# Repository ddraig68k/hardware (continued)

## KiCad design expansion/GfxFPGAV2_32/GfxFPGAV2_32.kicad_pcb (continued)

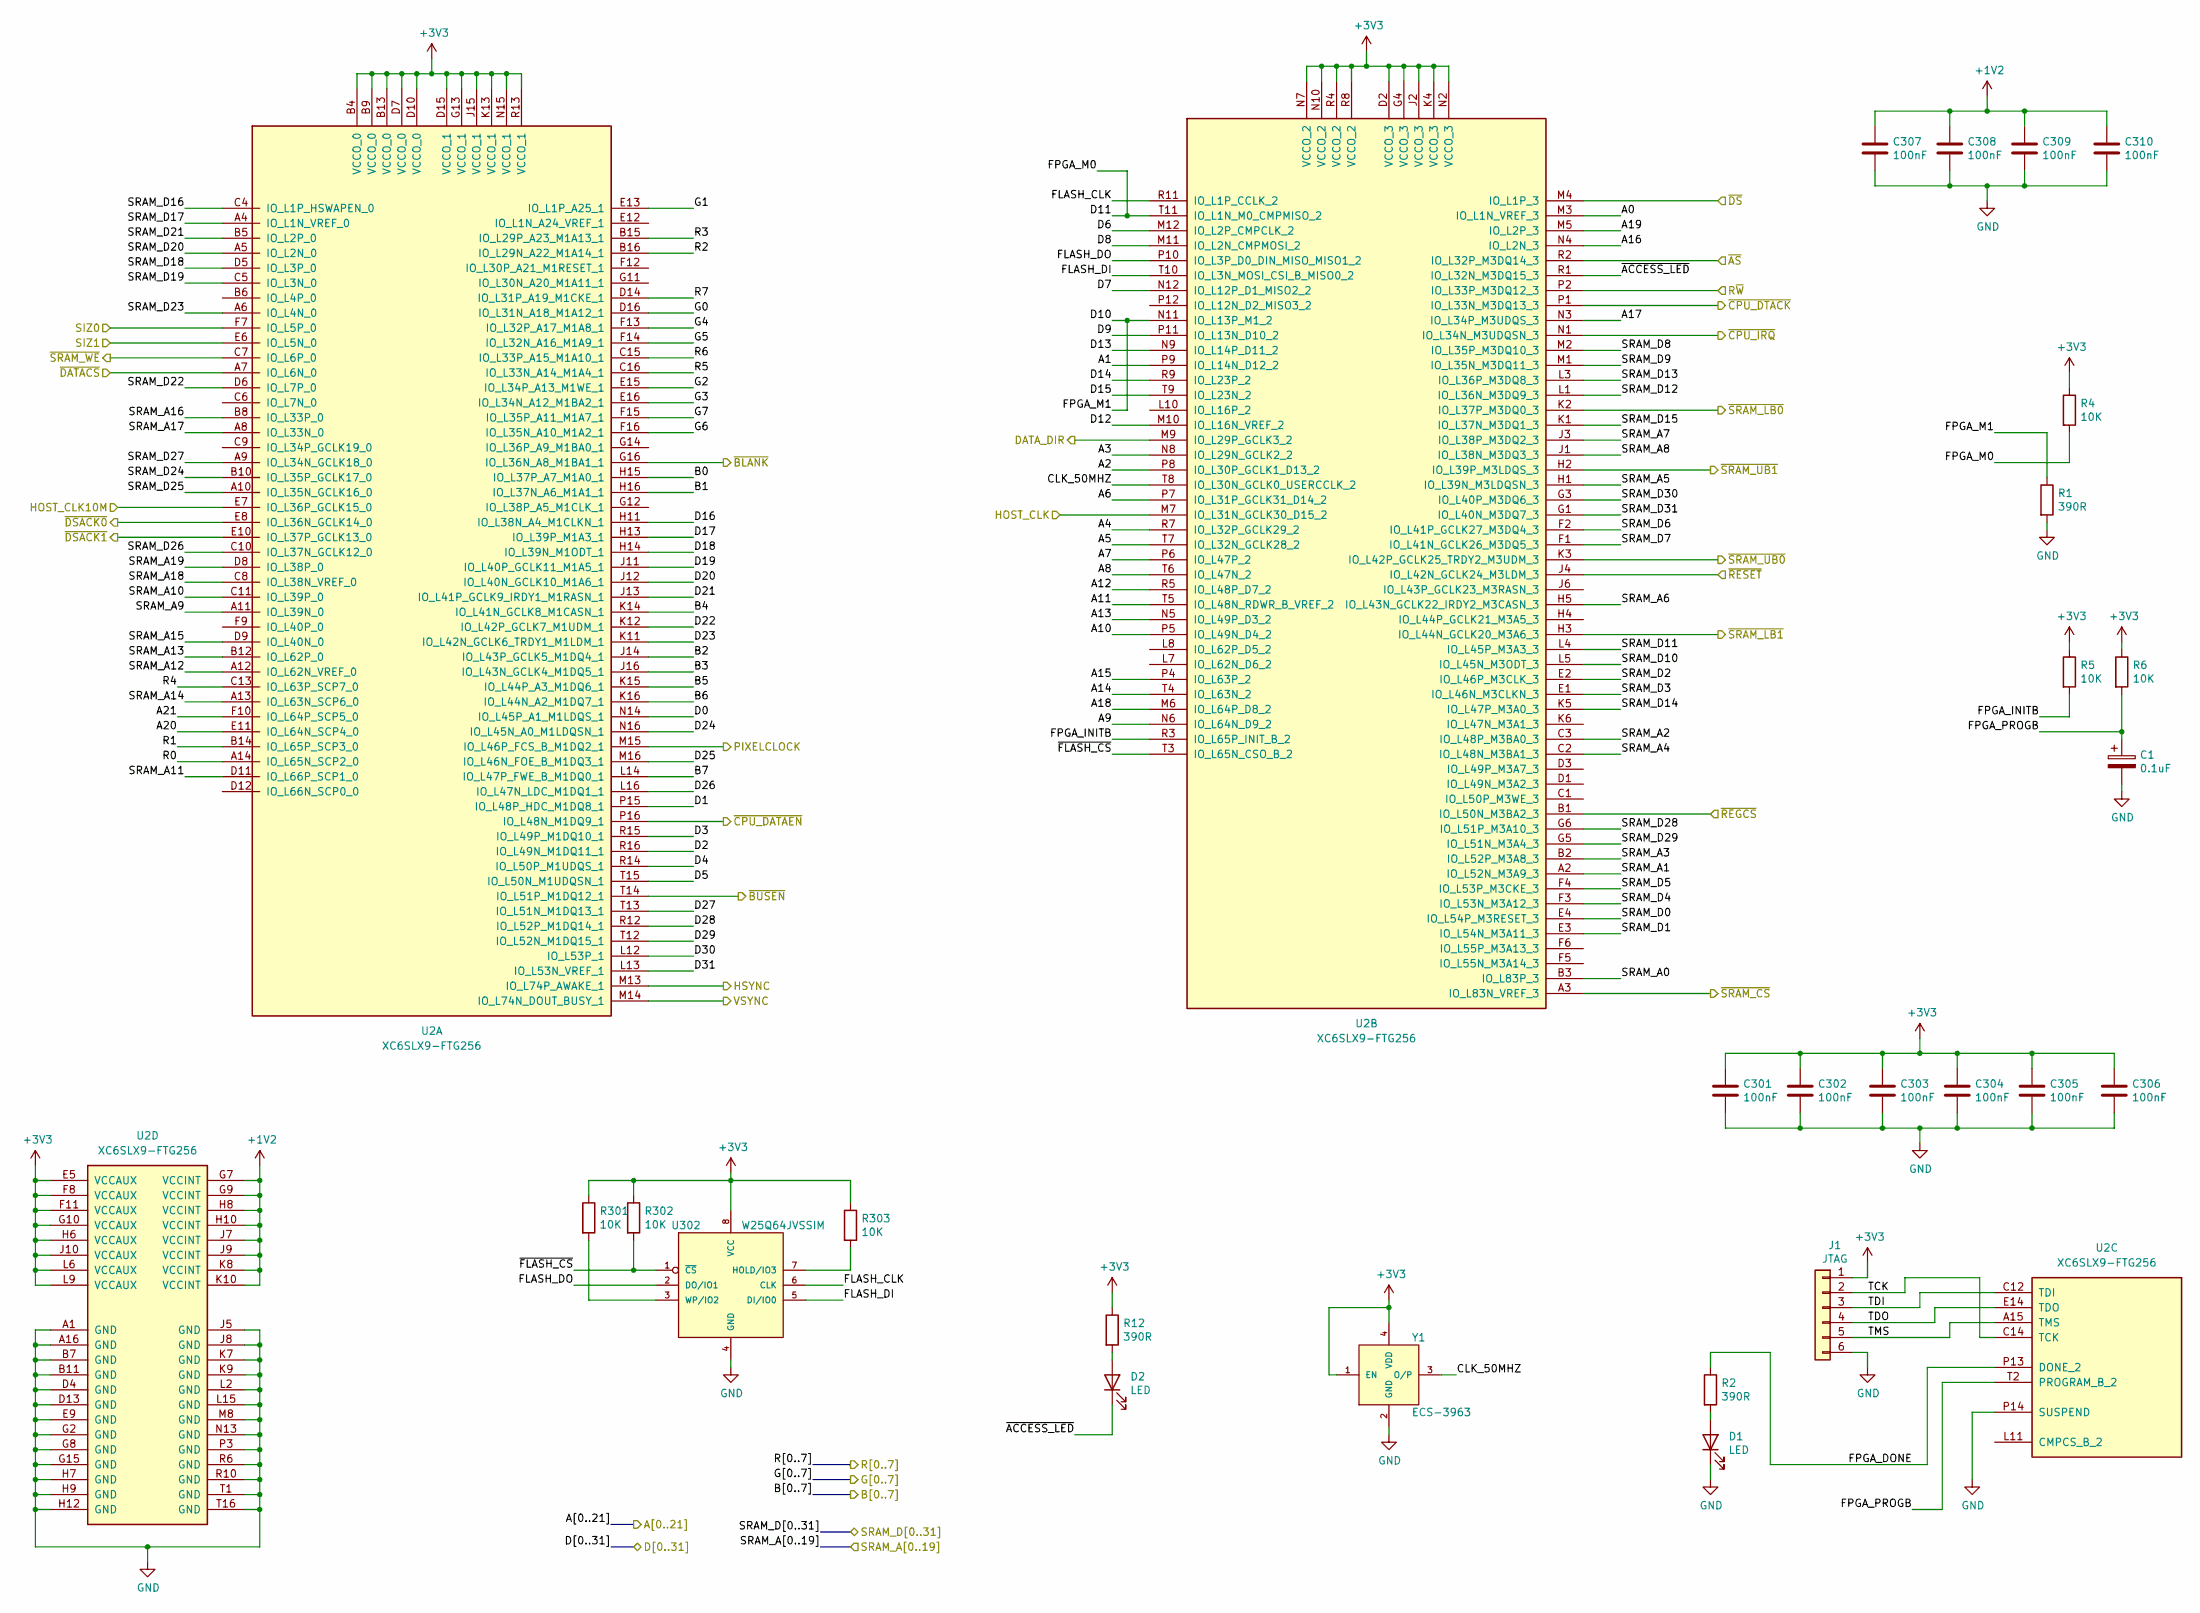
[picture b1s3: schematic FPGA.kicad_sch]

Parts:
C1: 0.1uF; CP_Elec_4x5.3
C301, C302, C303, C304, C305, C306, C307, C308, C309, C310: 100nF; C_0805_2012Metric
D1, D2: LED; LED_1206_3216Metric
J1: JTAG; PinHeader_1x06_P2.54mm_Vertical
R1, R2, R12: 390R; R_0805_2012Metric
R4, R5, R6, R301, R302, R303: 10K; R_0805_2012Metric
U2: XC6SLX9-FTG256; Xilinx_FTG256
U302: W25Q64JVSSIM; SOIC127P790X195-8N
Y1: ECS-3963; OSC_ECS-3963; PARTREV N/A

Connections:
+1V2: C307.1, C308.1, C309.1, C310.1, U2.G7 (VCCINT), U2.G9 (VCCINT), U2.H8 (VCCINT), U2.H10 (VCCINT), U2.J7 (VCCINT), U2.J9 (VCCINT), U2.K8 (VCCINT), U2.K10 (VCCINT); also elsewhere on the board
+3V3: C301.1, C302.1, C303.1, C304.1, C305.1, C306.1, J1.1, R4.1, R5.1, R6.1, R12.1, R301.1, R302.1, R303.1, U2.B4 (VCCO_0), U2.B9 (VCCO_0), U2.B13 (VCCO_0), U2.D2 (VCCO_3), U2.D7 (VCCO_0), U2.D10 (VCCO_0), U2.D15 (VCCO_1), U2.E5 (VCCAUX), U2.F8 (VCCAUX), U2.F11 (VCCAUX), U2.G4 (VCCO_3), U2.G10 (VCCAUX), U2.G13 (VCCO_1), U2.H6 (VCCAUX), U2.J2 (VCCO_3), U2.J10 (VCCAUX), U2.J15 (VCCO_1), U2.K4 (VCCO_3), U2.K13 (VCCO_1), U2.L6 (VCCAUX), U2.L9 (VCCAUX), U2.N2 (VCCO_3), U2.N7 (VCCO_2), U2.N10 (VCCO_2), U2.N15 (VCCO_1), U2.R4 (VCCO_2), U2.R8 (VCCO_2), U2.R13 (VCCO_1), U302.8 (VCC), Y1.1 (EN), Y1.4 (VDD); also elsewhere on the board
/FPGA/A0: U2.M3 (IO_L1N_VREF_3); also elsewhere on the board
/FPGA/A1: U2.P9 (IO_L14N_D12_2); also elsewhere on the board
/FPGA/A2: U2.P8 (IO_L30P_GCLK1_D13_2); also elsewhere on the board
/FPGA/A3: U2.N8 (IO_L29N_GCLK2_2); also elsewhere on the board
/FPGA/A4: U2.R7 (IO_L32P_GCLK29_2); also elsewhere on the board
/FPGA/A5: U2.T7 (IO_L32N_GCLK28_2); also elsewhere on the board
/FPGA/A6: U2.P7 (IO_L31P_GCLK31_D14_2); also elsewhere on the board
/FPGA/A7: U2.P6 (IO_L47P_2); also elsewhere on the board
/FPGA/A8: U2.T6 (IO_L47N_2); also elsewhere on the board
/FPGA/A9: U2.N6 (IO_L64N_D9_2); also elsewhere on the board
/FPGA/A10: U2.P5 (IO_L49N_D4_2); also elsewhere on the board
/FPGA/A11: U2.T5 (IO_L48N_RDWR_B_VREF_2); also elsewhere on the board
/FPGA/A12: U2.R5 (IO_L48P_D7_2); also elsewhere on the board
/FPGA/A13: U2.N5 (IO_L49P_D3_2); also elsewhere on the board
/FPGA/A14: U2.T4 (IO_L63N_2); also elsewhere on the board
/FPGA/A15: U2.P4 (IO_L63P_2); also elsewhere on the board
/FPGA/A16: U2.N4 (IO_L2N_3); also elsewhere on the board
/FPGA/A17: U2.N3 (IO_L34P_M3UDQS_3); also elsewhere on the board
/FPGA/A18: U2.M6 (IO_L64P_D8_2); also elsewhere on the board
/FPGA/A19: U2.M5 (IO_L2P_3); also elsewhere on the board
/FPGA/A20: U2.E11 (IO_L64N_SCP4_0); also elsewhere on the board
/FPGA/A21: U2.F10 (IO_L64P_SCP5_0); also elsewhere on the board
/FPGA/B0: U2.H15 (IO_L37P_A7_M1A0_1); also elsewhere on the board
/FPGA/B1: U2.H16 (IO_L37N_A6_M1A1_1); also elsewhere on the board
/FPGA/B2: U2.J14 (IO_L43P_GCLK5_M1DQ4_1); also elsewhere on the board
/FPGA/B3: U2.J16 (IO_L43N_GCLK4_M1DQ5_1); also elsewhere on the board
/FPGA/B4: U2.K14 (IO_L41N_GCLK8_M1CASN_1); also elsewhere on the board
/FPGA/B5: U2.K15 (IO_L44P_A3_M1DQ6_1); also elsewhere on the board
/FPGA/B6: U2.K16 (IO_L44N_A2_M1DQ7_1); also elsewhere on the board
/FPGA/B7: U2.L14 (IO_L47P_FWE_B_M1DQ0_1); also elsewhere on the board
/FPGA/CLK_50MHZ: U2.T8 (IO_L30N_GCLK0_USERCCLK_2), Y1.3 (O/P)
/FPGA/D0: U2.N14 (IO_L45P_A1_M1LDQS_1); also elsewhere on the board
/FPGA/D1: U2.P15 (IO_L48P_HDC_M1DQ8_1); also elsewhere on the board
/FPGA/D2: U2.R16 (IO_L49N_M1DQ11_1); also elsewhere on the board
/FPGA/D3: U2.R15 (IO_L49P_M1DQ10_1); also elsewhere on the board
/FPGA/D4: U2.R14 (IO_L50P_M1UDQS_1); also elsewhere on the board
/FPGA/D5: U2.T15 (IO_L50N_M1UDQSN_1); also elsewhere on the board
/FPGA/D6: U2.M12 (IO_L2P_CMPCLK_2); also elsewhere on the board
/FPGA/D7: U2.N12 (IO_L12P_D1_MISO2_2); also elsewhere on the board
/FPGA/D8: U2.M11 (IO_L2N_CMPMOSI_2); also elsewhere on the board
/FPGA/D9: U2.P11 (IO_L13N_D10_2); also elsewhere on the board
/FPGA/D10: R1.1, U2.N11 (IO_L13P_M1_2); also elsewhere on the board
/FPGA/D11: R4.2, U2.T11 (IO_L1N_M0_CMPMISO_2); also elsewhere on the board
/FPGA/D12: U2.M10 (IO_L16N_VREF_2); also elsewhere on the board
/FPGA/D13: U2.N9 (IO_L14P_D11_2); also elsewhere on the board
/FPGA/D14: U2.R9 (IO_L23P_2); also elsewhere on the board
/FPGA/D15: U2.T9 (IO_L23N_2); also elsewhere on the board
/FPGA/D16: U2.H11 (IO_L38N_A4_M1CLKN_1); also elsewhere on the board
/FPGA/D17: U2.H13 (IO_L39P_M1A3_1); also elsewhere on the board
/FPGA/D18: U2.H14 (IO_L39N_M1ODT_1); also elsewhere on the board
/FPGA/D19: U2.J11 (IO_L40P_GCLK11_M1A5_1); also elsewhere on the board
/FPGA/D20: U2.J12 (IO_L40N_GCLK10_M1A6_1); also elsewhere on the board
/FPGA/D21: U2.J13 (IO_L41P_GCLK9_IRDY1_M1RASN_1); also elsewhere on the board
/FPGA/D22: U2.K12 (IO_L42P_GCLK7_M1UDM_1); also elsewhere on the board
/FPGA/D23: U2.K11 (IO_L42N_GCLK6_TRDY1_M1LDM_1); also elsewhere on the board
/FPGA/D24: U2.N16 (IO_L45N_A0_M1LDQSN_1); also elsewhere on the board
/FPGA/D25: U2.M16 (IO_L46N_FOE_B_M1DQ3_1); also elsewhere on the board
/FPGA/D26: U2.L16 (IO_L47N_LDC_M1DQ1_1); also elsewhere on the board
/FPGA/D27: U2.T13 (IO_L51N_M1DQ13_1); also elsewhere on the board
/FPGA/D28: U2.R12 (IO_L52P_M1DQ14_1); also elsewhere on the board
/FPGA/D29: U2.T12 (IO_L52N_M1DQ15_1); also elsewhere on the board
/FPGA/D30: U2.L12 (IO_L53P_1); also elsewhere on the board
/FPGA/D31: U2.L13 (IO_L53N_VREF_1); also elsewhere on the board
/FPGA/DATA_DIR: U2.M9 (IO_L29P_GCLK3_2); also elsewhere on the board
/FPGA/FLASH_CLK: U2.R11 (IO_L1P_CCLK_2), U302.6 (CLK)
/FPGA/FLASH_DI: U2.T10 (IO_L3N_MOSI_CSI_B_MISO0_2), U302.5 (DI/IO0)
/FPGA/FLASH_DO: U2.P10 (IO_L3P_D0_DIN_MISO_MISO1_2), U302.2 (DO/IO1)
/FPGA/FPGA_DONE: R2.1, U2.P13 (DONE_2)
/FPGA/FPGA_INITB: R5.2, U2.R3 (IO_L65P_INIT_B_2)
/FPGA/FPGA_PROGB: C1.1, R6.2, U2.T2 (PROGRAM_B_2)
/FPGA/G0: U2.D16 (IO_L31N_A18_M1A12_1); also elsewhere on the board
/FPGA/G1: U2.E13 (IO_L1P_A25_1); also elsewhere on the board
/FPGA/G2: U2.E15 (IO_L34P_A13_M1WE_1); also elsewhere on the board
/FPGA/G3: U2.E16 (IO_L34N_A12_M1BA2_1); also elsewhere on the board
/FPGA/G4: U2.F13 (IO_L32P_A17_M1A8_1); also elsewhere on the board
/FPGA/G5: U2.F14 (IO_L32N_A16_M1A9_1); also elsewhere on the board
/FPGA/G6: U2.F16 (IO_L35N_A10_M1A2_1); also elsewhere on the board
/FPGA/G7: U2.F15 (IO_L35P_A11_M1A7_1); also elsewhere on the board
/FPGA/HOST_CLK: U2.M7 (IO_L31N_GCLK30_D15_2); also elsewhere on the board
/FPGA/HOST_CLK10M: U2.E7 (IO_L36P_GCLK15_0); also elsewhere on the board
/FPGA/HSYNC: U2.M13 (IO_L74P_AWAKE_1); also elsewhere on the board
/FPGA/PIXELCLOCK: U2.M15 (IO_L46P_FCS_B_M1DQ2_1); also elsewhere on the board
/FPGA/R0: U2.A14 (IO_L65N_SCP2_0); also elsewhere on the board
/FPGA/R1: U2.B14 (IO_L65P_SCP3_0); also elsewhere on the board
/FPGA/R2: U2.B16 (IO_L29N_A22_M1A14_1); also elsewhere on the board
/FPGA/R3: U2.B15 (IO_L29P_A23_M1A13_1); also elsewhere on the board
/FPGA/R4: U2.C13 (IO_L63P_SCP7_0); also elsewhere on the board
/FPGA/R5: U2.C16 (IO_L33N_A14_M1A4_1); also elsewhere on the board
/FPGA/R6: U2.C15 (IO_L33P_A15_M1A10_1); also elsewhere on the board
/FPGA/R7: U2.D14 (IO_L31P_A19_M1CKE_1); also elsewhere on the board
/FPGA/R~W: U2.P2 (IO_L33P_M3DQ12_3); also elsewhere on the board
/FPGA/SIZ0: U2.F7 (IO_L5P_0); also elsewhere on the board
/FPGA/SIZ1: U2.E6 (IO_L5N_0); also elsewhere on the board
/FPGA/SRAM_A0: U2.B3 (IO_L83P_3); also elsewhere on the board
/FPGA/SRAM_A1: U2.A2 (IO_L52N_M3A9_3); also elsewhere on the board
/FPGA/SRAM_A2: U2.C3 (IO_L48P_M3BA0_3); also elsewhere on the board
/FPGA/SRAM_A3: U2.B2 (IO_L52P_M3A8_3); also elsewhere on the board
/FPGA/SRAM_A4: U2.C2 (IO_L48N_M3BA1_3); also elsewhere on the board
/FPGA/SRAM_A5: U2.H1 (IO_L39N_M3LDQSN_3); also elsewhere on the board
/FPGA/SRAM_A6: U2.H5 (IO_L43N_GCLK22_IRDY2_M3CASN_3); also elsewhere on the board
/FPGA/SRAM_A7: U2.J3 (IO_L38P_M3DQ2_3); also elsewhere on the board
/FPGA/SRAM_A8: U2.J1 (IO_L38N_M3DQ3_3); also elsewhere on the board
/FPGA/SRAM_A9: U2.A11 (IO_L39N_0); also elsewhere on the board
/FPGA/SRAM_A10: U2.C11 (IO_L39P_0); also elsewhere on the board
/FPGA/SRAM_A11: U2.D11 (IO_L66P_SCP1_0); also elsewhere on the board
/FPGA/SRAM_A12: U2.A12 (IO_L62N_VREF_0); also elsewhere on the board
/FPGA/SRAM_A13: U2.B12 (IO_L62P_0); also elsewhere on the board
/FPGA/SRAM_A14: U2.A13 (IO_L63N_SCP6_0); also elsewhere on the board
/FPGA/SRAM_A15: U2.D9 (IO_L40N_0); also elsewhere on the board
/FPGA/SRAM_A16: U2.B8 (IO_L33P_0); also elsewhere on the board
/FPGA/SRAM_A17: U2.A8 (IO_L33N_0); also elsewhere on the board
/FPGA/SRAM_A18: U2.C8 (IO_L38N_VREF_0); also elsewhere on the board
/FPGA/SRAM_A19: U2.D8 (IO_L38P_0); also elsewhere on the board
/FPGA/SRAM_D0: U2.E4 (IO_L54P_M3RESET_3); also elsewhere on the board
/FPGA/SRAM_D1: U2.E3 (IO_L54N_M3A11_3); also elsewhere on the board
/FPGA/SRAM_D2: U2.E2 (IO_L46P_M3CLK_3); also elsewhere on the board
/FPGA/SRAM_D3: U2.E1 (IO_L46N_M3CLKN_3); also elsewhere on the board
/FPGA/SRAM_D4: U2.F3 (IO_L53N_M3A12_3); also elsewhere on the board
/FPGA/SRAM_D5: U2.F4 (IO_L53P_M3CKE_3); also elsewhere on the board
/FPGA/SRAM_D6: U2.F2 (IO_L41P_GCLK27_M3DQ4_3); also elsewhere on the board
/FPGA/SRAM_D7: U2.F1 (IO_L41N_GCLK26_M3DQ5_3); also elsewhere on the board
/FPGA/SRAM_D8: U2.M2 (IO_L35P_M3DQ10_3); also elsewhere on the board
/FPGA/SRAM_D9: U2.M1 (IO_L35N_M3DQ11_3); also elsewhere on the board
/FPGA/SRAM_D10: U2.L5 (IO_L45N_M3ODT_3); also elsewhere on the board
/FPGA/SRAM_D11: U2.L4 (IO_L45P_M3A3_3); also elsewhere on the board
/FPGA/SRAM_D12: U2.L1 (IO_L36N_M3DQ9_3); also elsewhere on the board
/FPGA/SRAM_D13: U2.L3 (IO_L36P_M3DQ8_3); also elsewhere on the board
/FPGA/SRAM_D14: U2.K5 (IO_L47P_M3A0_3); also elsewhere on the board
/FPGA/SRAM_D15: U2.K1 (IO_L37N_M3DQ1_3); also elsewhere on the board
/FPGA/SRAM_D16: U2.C4 (IO_L1P_HSWAPEN_0); also elsewhere on the board
/FPGA/SRAM_D17: U2.A4 (IO_L1N_VREF_0); also elsewhere on the board
/FPGA/SRAM_D18: U2.D5 (IO_L3P_0); also elsewhere on the board
/FPGA/SRAM_D19: U2.C5 (IO_L3N_0); also elsewhere on the board
/FPGA/SRAM_D20: U2.A5 (IO_L2N_0); also elsewhere on the board
/FPGA/SRAM_D21: U2.B5 (IO_L2P_0); also elsewhere on the board
/FPGA/SRAM_D22: U2.D6 (IO_L7P_0); also elsewhere on the board
/FPGA/SRAM_D23: U2.A6 (IO_L4N_0); also elsewhere on the board
/FPGA/SRAM_D24: U2.B10 (IO_L35P_GCLK17_0); also elsewhere on the board
/FPGA/SRAM_D25: U2.A10 (IO_L35N_GCLK16_0); also elsewhere on the board
/FPGA/SRAM_D26: U2.C10 (IO_L37N_GCLK12_0); also elsewhere on the board
/FPGA/SRAM_D27: U2.A9 (IO_L34N_GCLK18_0); also elsewhere on the board
/FPGA/SRAM_D28: U2.G6 (IO_L51P_M3A10_3); also elsewhere on the board
/FPGA/SRAM_D29: U2.G5 (IO_L51N_M3A4_3); also elsewhere on the board
/FPGA/SRAM_D30: U2.G3 (IO_L40P_M3DQ6_3); also elsewhere on the board
/FPGA/SRAM_D31: U2.G1 (IO_L40N_M3DQ7_3); also elsewhere on the board
/FPGA/TCK: J1.2, U2.C14 (TCK)
/FPGA/TDI: J1.3, U2.C12 (TDI)
/FPGA/TDO: J1.4, U2.E14 (TDO)
/FPGA/TMS: J1.5, U2.A15 (TMS)
/FPGA/VSYNC: U2.M14 (IO_L74N_DOUT_BUSY_1); also elsewhere on the board
/FPGA/~ACCESS_LED: D2.1 (K), U2.R1 (IO_L32N_M3DQ15_3)
/FPGA/~AS: U2.R2 (IO_L32P_M3DQ14_3); also elsewhere on the board
/FPGA/~BLANK: U2.G16 (IO_L36N_A8_M1BA1_1); also elsewhere on the board
/FPGA/~BUSEN: U2.T14 (IO_L51P_M1DQ12_1); also elsewhere on the board
/FPGA/~CPU_DATAEN: U2.P16 (IO_L48N_M1DQ9_1); also elsewhere on the board
/FPGA/~DATACS: U2.A7 (IO_L6N_0); also elsewhere on the board
/FPGA/~DS: U2.M4 (IO_L1P_3); also elsewhere on the board
/FPGA/~FLASH_CS: R302.2, U2.T3 (IO_L65N_CSO_B_2), U302.1 (~CS)
/FPGA/~REGCS: U2.B1 (IO_L50N_M3BA2_3); also elsewhere on the board
/FPGA/~RESET: U2.J4 (IO_L42N_GCLK24_M3LDM_3); also elsewhere on the board
/FPGA/~SRAM_CS: U2.A3 (IO_L83N_VREF_3); also elsewhere on the board
/FPGA/~SRAM_LB0: U2.K2 (IO_L37P_M3DQ0_3); also elsewhere on the board
/FPGA/~SRAM_LB1: U2.H3 (IO_L44N_GCLK20_M3A6_3); also elsewhere on the board
/FPGA/~SRAM_UB0: U2.K3 (IO_L42P_GCLK25_TRDY2_M3UDM_3); also elsewhere on the board
/FPGA/~SRAM_UB1: U2.H2 (IO_L39P_M3LDQS_3); also elsewhere on the board
/FPGA/~SRAM_WE: U2.C7 (IO_L6P_0); also elsewhere on the board
/~CPU_DSACK0: U2.E8 (IO_L36N_GCLK14_0); also elsewhere on the board
/~CPU_DSACK1: U2.E10 (IO_L37P_GCLK13_0); also elsewhere on the board
/~CPU_DTACK: U2.P1 (IO_L33N_M3DQ13_3); also elsewhere on the board
/~CPU_IRQ: U2.N1 (IO_L34N_M3UDQSN_3); also elsewhere on the board
GND: C1.2, C301.2, C302.2, C303.2, C304.2, C305.2, C306.2, C307.2, C308.2, C309.2, C310.2, D1.1 (K), J1.6, R1.2, U2.A1 (GND), U2.A16 (GND), U2.B7 (GND), U2.B11 (GND), U2.D4 (GND), U2.D13 (GND), U2.E9 (GND), U2.G2 (GND), U2.G8 (GND), U2.G15 (GND), U2.H7 (GND), U2.H9 (GND), U2.H12 (GND), U2.J5 (GND), U2.J8 (GND), U2.K7 (GND), U2.K9 (GND), U2.L2 (GND), U2.L15 (GND), U2.M8 (GND), U2.N13 (GND), U2.P3 (GND), U2.P14 (SUSPEND), U2.R6 (GND), U2.R10 (GND), U2.T1 (GND), U2.T16 (GND), U302.4 (GND), Y1.2 (GND); also elsewhere on the board
unnamed: D1.2 (A), R2.2
unnamed: D2.2 (A), R12.2
unnamed: R303.2, U302.7 (HOLD/IO3)
unnamed: R301.2, U302.3 (WP/IO2)

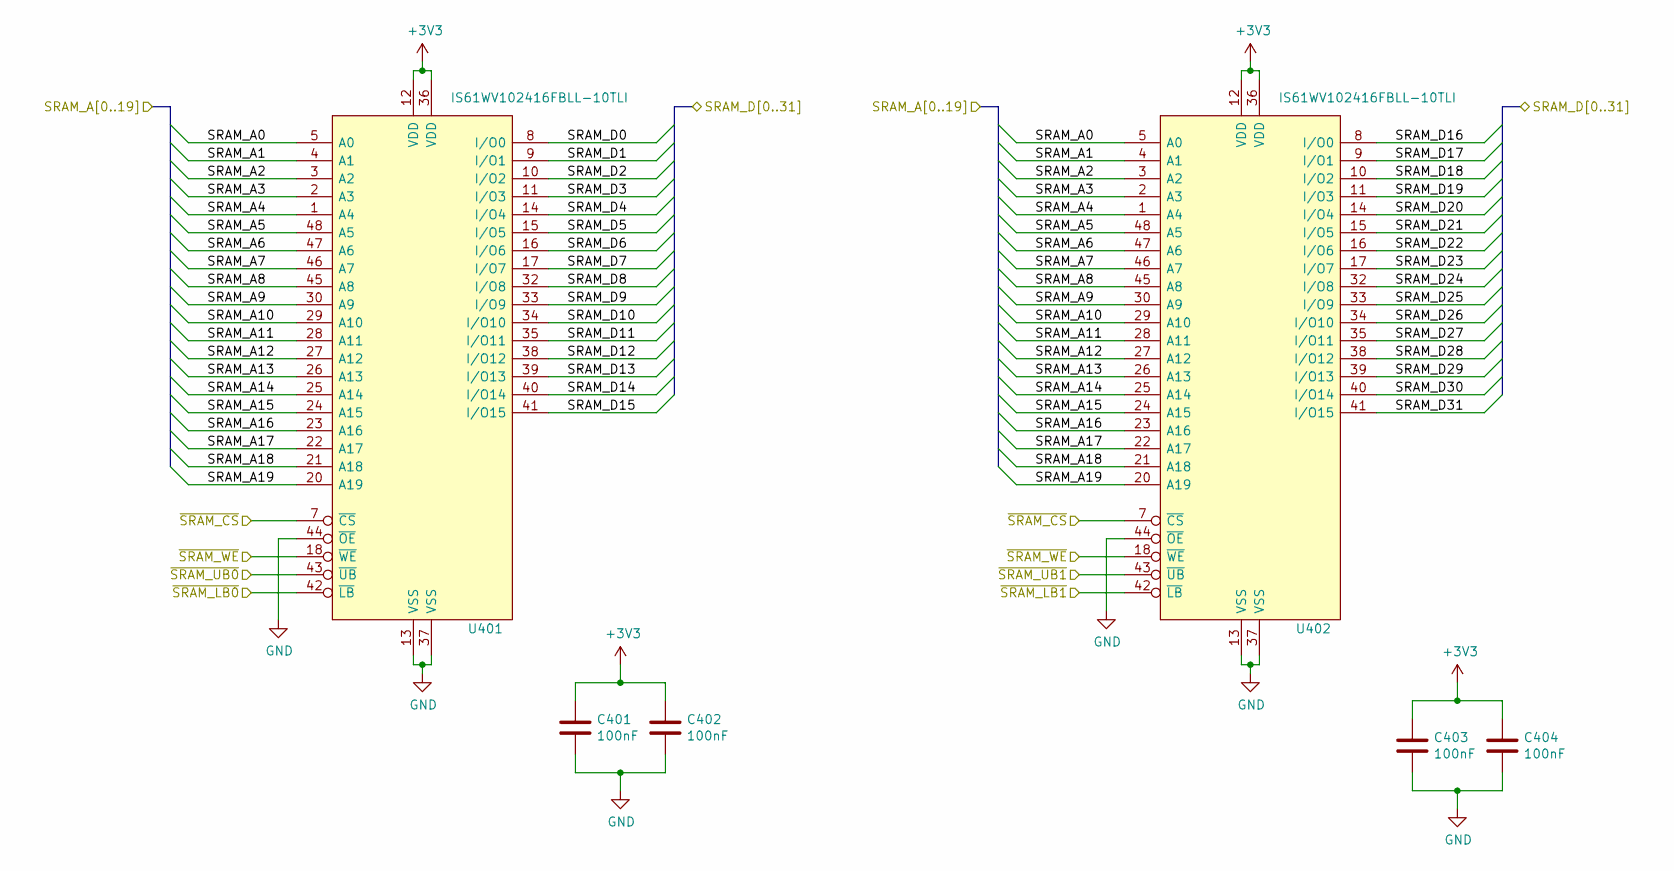
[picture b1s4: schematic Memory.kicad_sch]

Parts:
C401, C402, C403, C404: 100nF; C_0805_2012Metric
U401, U402: IS61WV102416FBLL-10TLI; SOP50P2000X120-48N; Manufacturer_Part_Number IS61WV102416FBLL-10TLI; Mouser Part Number 870-61WV12416FBL1TLI

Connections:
+3V3: C401.1, C402.1, C403.1, C404.1, U401.12 (VDD), U401.36 (VDD), U402.12 (VDD), U402.36 (VDD); also elsewhere on the board
/FPGA/SRAM_A0: U401.5 (A0), U402.5 (A0); also elsewhere on the board
/FPGA/SRAM_A1: U401.4 (A1), U402.4 (A1); also elsewhere on the board
/FPGA/SRAM_A2: U401.3 (A2), U402.3 (A2); also elsewhere on the board
/FPGA/SRAM_A3: U401.2 (A3), U402.2 (A3); also elsewhere on the board
/FPGA/SRAM_A4: U401.1 (A4), U402.1 (A4); also elsewhere on the board
/FPGA/SRAM_A5: U401.48 (A5), U402.48 (A5); also elsewhere on the board
/FPGA/SRAM_A6: U401.47 (A6), U402.47 (A6); also elsewhere on the board
/FPGA/SRAM_A7: U401.46 (A7), U402.46 (A7); also elsewhere on the board
/FPGA/SRAM_A8: U401.45 (A8), U402.45 (A8); also elsewhere on the board
/FPGA/SRAM_A9: U401.30 (A9), U402.30 (A9); also elsewhere on the board
/FPGA/SRAM_A10: U401.29 (A10), U402.29 (A10); also elsewhere on the board
/FPGA/SRAM_A11: U401.28 (A11), U402.28 (A11); also elsewhere on the board
/FPGA/SRAM_A12: U401.27 (A12), U402.27 (A12); also elsewhere on the board
/FPGA/SRAM_A13: U401.26 (A13), U402.26 (A13); also elsewhere on the board
/FPGA/SRAM_A14: U401.25 (A14), U402.25 (A14); also elsewhere on the board
/FPGA/SRAM_A15: U401.24 (A15), U402.24 (A15); also elsewhere on the board
/FPGA/SRAM_A16: U401.23 (A16), U402.23 (A16); also elsewhere on the board
/FPGA/SRAM_A17: U401.22 (A17), U402.22 (A17); also elsewhere on the board
/FPGA/SRAM_A18: U401.21 (A18), U402.21 (A18); also elsewhere on the board
/FPGA/SRAM_A19: U401.20 (A19), U402.20 (A19); also elsewhere on the board
/FPGA/SRAM_D0: U401.8 (I/O0); also elsewhere on the board
/FPGA/SRAM_D1: U401.9 (I/O1); also elsewhere on the board
/FPGA/SRAM_D2: U401.10 (I/O2); also elsewhere on the board
/FPGA/SRAM_D3: U401.11 (I/O3); also elsewhere on the board
/FPGA/SRAM_D4: U401.14 (I/O4); also elsewhere on the board
/FPGA/SRAM_D5: U401.15 (I/O5); also elsewhere on the board
/FPGA/SRAM_D6: U401.16 (I/O6); also elsewhere on the board
/FPGA/SRAM_D7: U401.17 (I/O7); also elsewhere on the board
/FPGA/SRAM_D8: U401.32 (I/O8); also elsewhere on the board
/FPGA/SRAM_D9: U401.33 (I/O9); also elsewhere on the board
/FPGA/SRAM_D10: U401.34 (I/O10); also elsewhere on the board
/FPGA/SRAM_D11: U401.35 (I/O11); also elsewhere on the board
/FPGA/SRAM_D12: U401.38 (I/O12); also elsewhere on the board
/FPGA/SRAM_D13: U401.39 (I/O13); also elsewhere on the board
/FPGA/SRAM_D14: U401.40 (I/O14); also elsewhere on the board
/FPGA/SRAM_D15: U401.41 (I/O15); also elsewhere on the board
/FPGA/SRAM_D16: U402.8 (I/O0); also elsewhere on the board
/FPGA/SRAM_D17: U402.9 (I/O1); also elsewhere on the board
/FPGA/SRAM_D18: U402.10 (I/O2); also elsewhere on the board
/FPGA/SRAM_D19: U402.11 (I/O3); also elsewhere on the board
/FPGA/SRAM_D20: U402.14 (I/O4); also elsewhere on the board
/FPGA/SRAM_D21: U402.15 (I/O5); also elsewhere on the board
/FPGA/SRAM_D22: U402.16 (I/O6); also elsewhere on the board
/FPGA/SRAM_D23: U402.17 (I/O7); also elsewhere on the board
/FPGA/SRAM_D24: U402.32 (I/O8); also elsewhere on the board
/FPGA/SRAM_D25: U402.33 (I/O9); also elsewhere on the board
/FPGA/SRAM_D26: U402.34 (I/O10); also elsewhere on the board
/FPGA/SRAM_D27: U402.35 (I/O11); also elsewhere on the board
/FPGA/SRAM_D28: U402.38 (I/O12); also elsewhere on the board
/FPGA/SRAM_D29: U402.39 (I/O13); also elsewhere on the board
/FPGA/SRAM_D30: U402.40 (I/O14); also elsewhere on the board
/FPGA/SRAM_D31: U402.41 (I/O15); also elsewhere on the board
/FPGA/~SRAM_CS: U401.7 (~CS), U402.7 (~CS); also elsewhere on the board
/FPGA/~SRAM_LB0: U401.42 (~LB); also elsewhere on the board
/FPGA/~SRAM_LB1: U402.42 (~LB); also elsewhere on the board
/FPGA/~SRAM_UB0: U401.43 (~UB); also elsewhere on the board
/FPGA/~SRAM_UB1: U402.43 (~UB); also elsewhere on the board
/FPGA/~SRAM_WE: U401.18 (~WE), U402.18 (~WE); also elsewhere on the board
GND: C401.2, C402.2, C403.2, C404.2, U401.13 (VSS), U401.37 (VSS), U401.44 (~OE), U402.13 (VSS), U402.37 (VSS), U402.44 (~OE); also elsewhere on the board

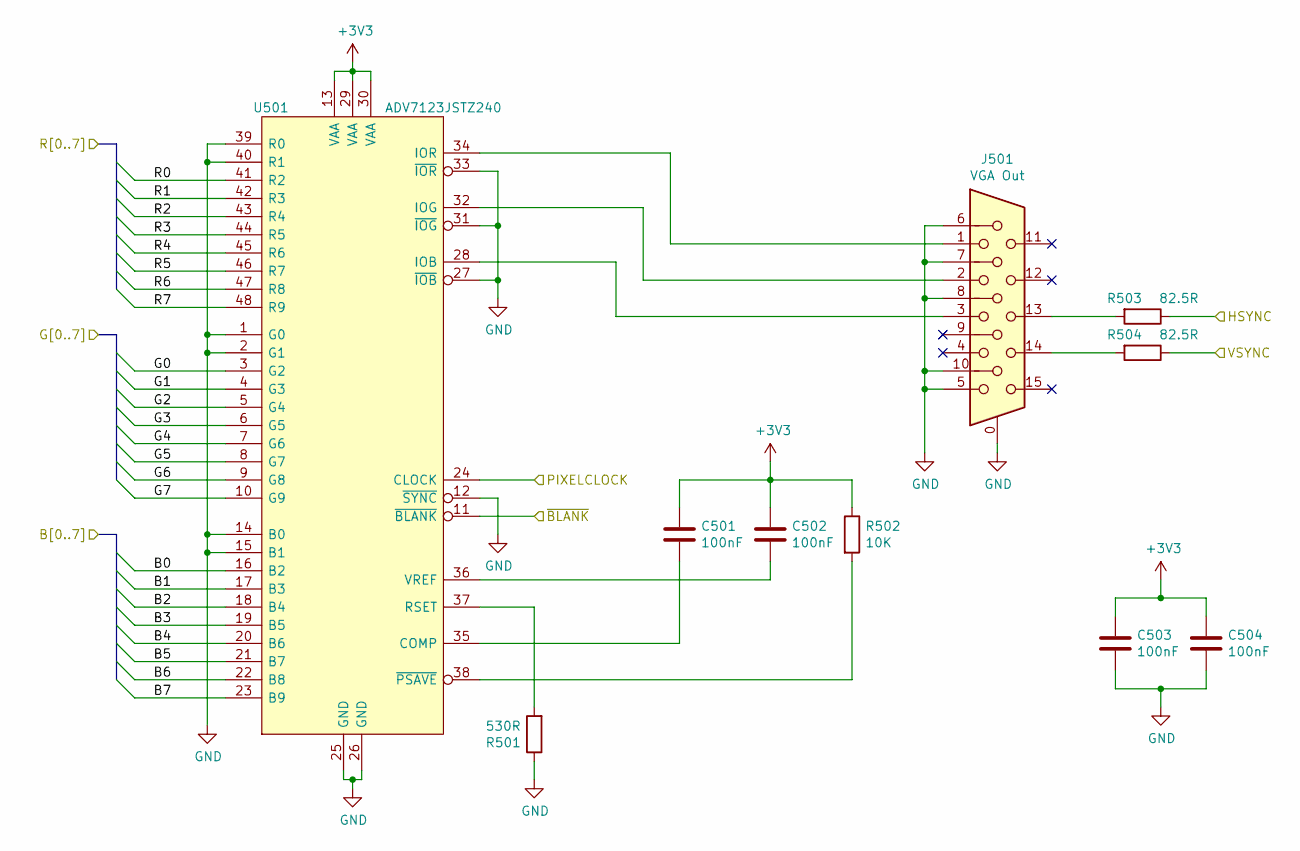
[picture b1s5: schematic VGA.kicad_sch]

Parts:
C501, C502, C503, C504: 100nF; C_0805_2012Metric
J501: VGA Out; DSUB-15-HD_Female_Horizontal_P2.29x1.98mm_EdgePinOffset3.03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
R501: 530R; R_0805_2012Metric
R502: 10K; R_0805_2012Metric
R503, R504: 82.5R; R_0805_2012Metric
U501: ADV7123JSTZ240; QFP50P900X900X160-48N; Manufacturer_Part_Number ADV7123JSTZ240; Mouser Part Number 584-ADV7123JSTZ240

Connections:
+3V3: C501.1, C502.1, C503.1, C504.1, R502.1, U501.13 (VAA), U501.29 (VAA), U501.30 (VAA); also elsewhere on the board
/FPGA/B0: U501.16 (B2); also elsewhere on the board
/FPGA/B1: U501.17 (B3); also elsewhere on the board
/FPGA/B2: U501.18 (B4); also elsewhere on the board
/FPGA/B3: U501.19 (B5); also elsewhere on the board
/FPGA/B4: U501.20 (B6); also elsewhere on the board
/FPGA/B5: U501.21 (B7); also elsewhere on the board
/FPGA/B6: U501.22 (B8); also elsewhere on the board
/FPGA/B7: U501.23 (B9); also elsewhere on the board
/FPGA/G0: U501.3 (G2); also elsewhere on the board
/FPGA/G1: U501.4 (G3); also elsewhere on the board
/FPGA/G2: U501.5 (G4); also elsewhere on the board
/FPGA/G3: U501.6 (G5); also elsewhere on the board
/FPGA/G4: U501.7 (G6); also elsewhere on the board
/FPGA/G5: U501.8 (G7); also elsewhere on the board
/FPGA/G6: U501.9 (G8); also elsewhere on the board
/FPGA/G7: U501.10 (G9); also elsewhere on the board
/FPGA/HSYNC: R503.1; also elsewhere on the board
/FPGA/PIXELCLOCK: U501.24 (CLOCK); also elsewhere on the board
/FPGA/R0: U501.41 (R2); also elsewhere on the board
/FPGA/R1: U501.42 (R3); also elsewhere on the board
/FPGA/R2: U501.43 (R4); also elsewhere on the board
/FPGA/R3: U501.44 (R5); also elsewhere on the board
/FPGA/R4: U501.45 (R6); also elsewhere on the board
/FPGA/R5: U501.46 (R7); also elsewhere on the board
/FPGA/R6: U501.47 (R8); also elsewhere on the board
/FPGA/R7: U501.48 (R9); also elsewhere on the board
/FPGA/VSYNC: R504.1; also elsewhere on the board
/FPGA/~BLANK: U501.11 (~BLANK); also elsewhere on the board
GND: C503.2, C504.2, J501.0, J501.5, J501.6, J501.7, J501.8, J501.10, R501.1, U501.1 (G0), U501.2 (G1), U501.12 (~SYNC), U501.14 (B0), U501.15 (B1), U501.25 (GND), U501.26 (GND), U501.27 (~IOB), U501.31 (~IOG), U501.33 (~IOR), U501.39 (R0), U501.40 (R1); also elsewhere on the board
unnamed: J501.13, R503.2
unnamed: J501.14, R504.2
unnamed: C501.2, U501.35 (COMP)
unnamed: J501.3, U501.28 (IOB)
unnamed: J501.2, U501.32 (IOG)
unnamed: J501.1, U501.34 (IOR)
unnamed: R501.2, U501.37 (RSET)
unnamed: C502.2, U501.36 (VREF)
unnamed: R502.2, U501.38 (~PSAVE)

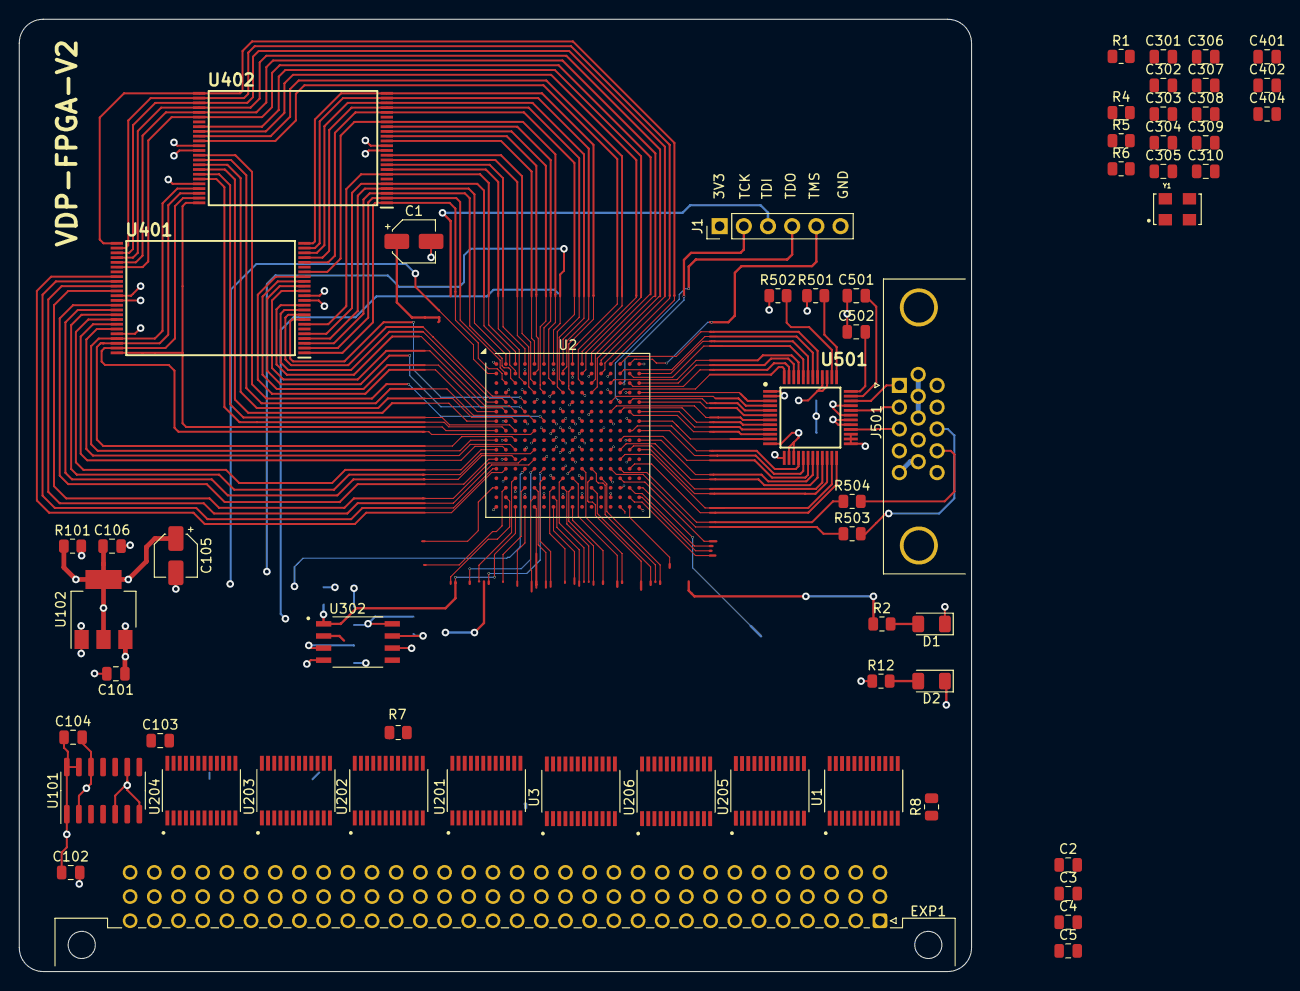
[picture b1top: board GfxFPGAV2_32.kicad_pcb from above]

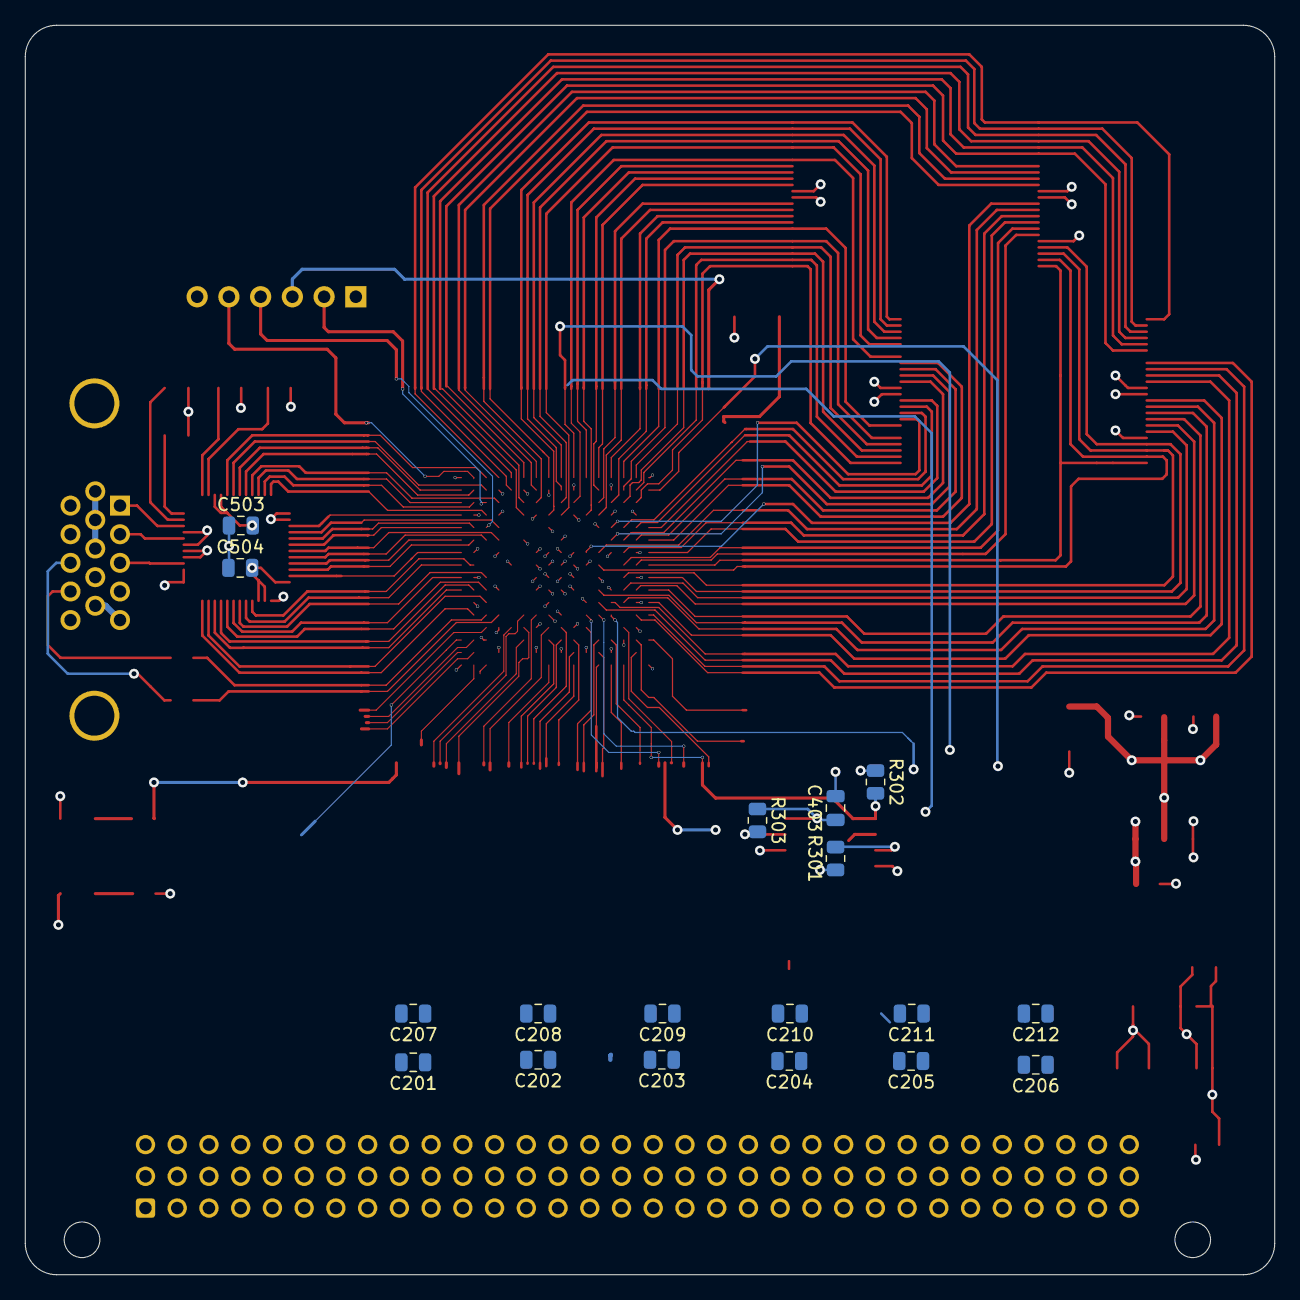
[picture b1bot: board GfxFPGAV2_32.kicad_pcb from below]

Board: 4 copper layers, 100.0 x 100.0 mm, 78 parts (18 on the bottom side), 255 nets.
